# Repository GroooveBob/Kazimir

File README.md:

# Kazimir
Fightbox / Figtstick controler that runs wirh GP2040 firmware

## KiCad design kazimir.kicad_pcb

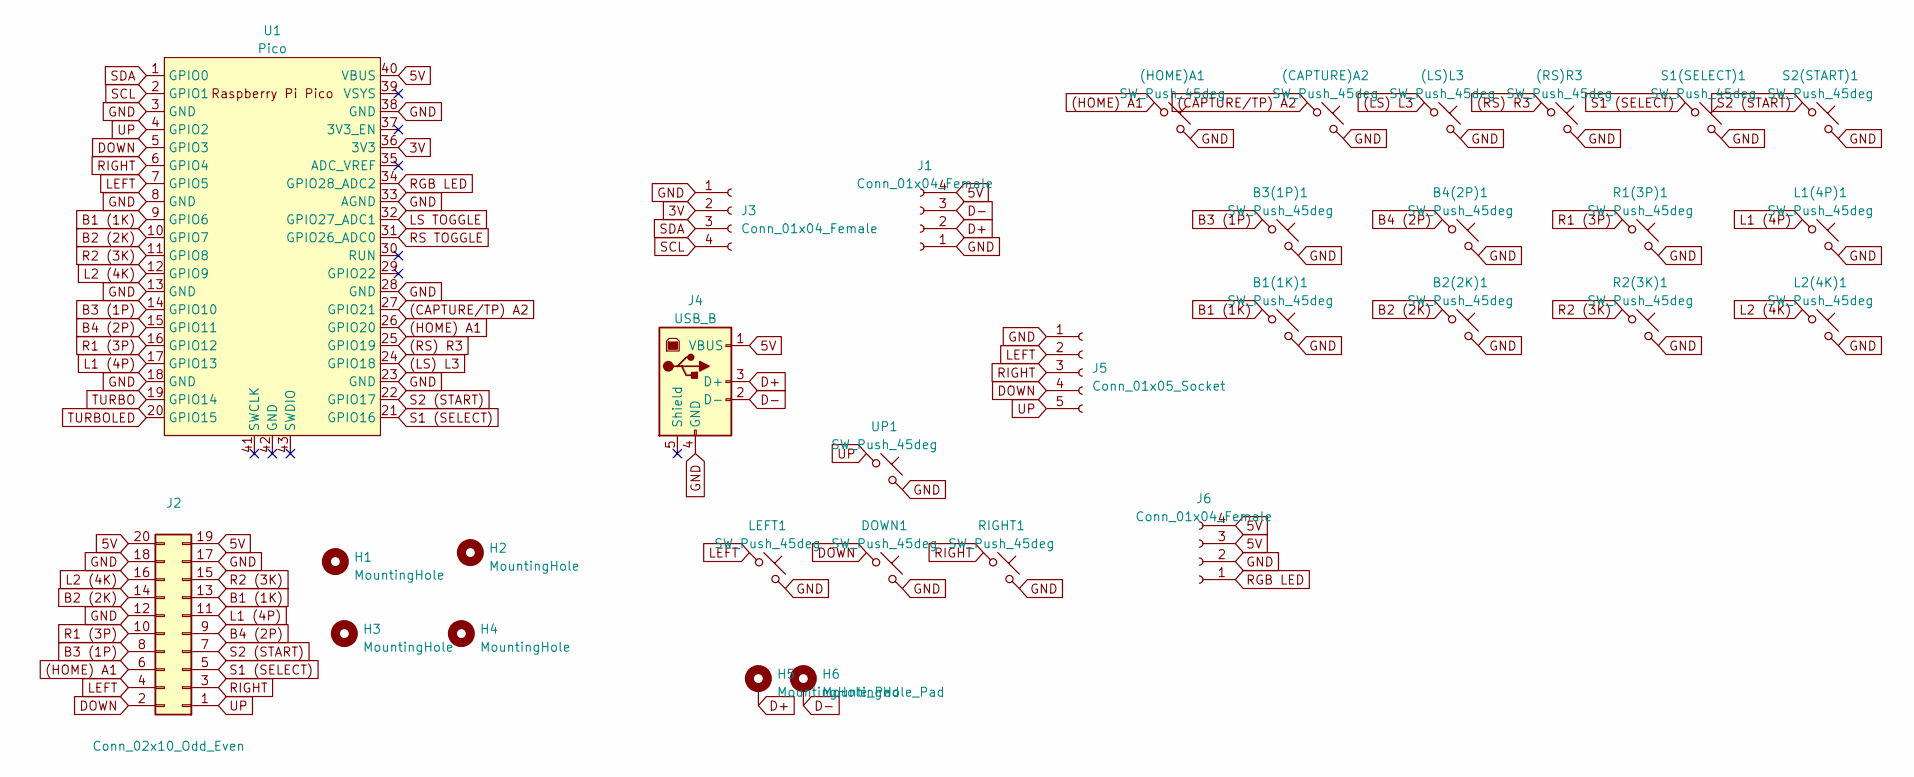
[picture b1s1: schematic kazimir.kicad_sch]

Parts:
(CAPTURE)A2: SW_Push_45deg; JST_XH_B2B-XH-A_1x02_P2.50mm_Verticalez
(HOME)A1: SW_Push_45deg; JST_XH_B2B-XH-A_1x02_P2.50mm_Verticalez
(LS)L3: SW_Push_45deg; JST_XH_B2B-XH-A_1x02_P2.50mm_Verticalez
(RS)R3: SW_Push_45deg; JST_XH_B2B-XH-A_1x02_P2.50mm_Verticalez
B1(1K)1, B2(2K)1, B3(1P)1, B4(2P)1: SW_Push_45deg; JST_XH_B2B-XH-A_1x02_P2.50mm_Verticalez
DOWN1: SW_Push_45deg; JST_XH_B2B-XH-A_1x02_P2.50mm_Verticalez
H1, H2, H3, H4: MountingHole; MountingHole_3.5mm_Pad_Via
H5, H6: MountingHole_Pad; TestPoint_Pad_2.5x2.5mm
J1, J3, J6: Conn_01x04_Female; JST_XH_B4B-XH-A_1x04_P2.50mm_Vertical
J2: Conn_02x10_Odd_Even; PinHeader_2x10_P2.54mm_Vertical
J4: USB_B; USB_B_Lumberg_2411_02_Horizontal
J5: Conn_01x05_Socket; JST_XH_B5B-XH-A_1x05_P2.50mm_Vertical
L1(4P)1, L2(4K)1: SW_Push_45deg; JST_XH_B2B-XH-A_1x02_P2.50mm_Verticalez
LEFT1: SW_Push_45deg; JST_XH_B2B-XH-A_1x02_P2.50mm_Verticalez
R1(3P)1, R2(3K)1: SW_Push_45deg; JST_XH_B2B-XH-A_1x02_P2.50mm_Verticalez
RIGHT1: SW_Push_45deg; JST_XH_B2B-XH-A_1x02_P2.50mm_Verticalez
S1(SELECT)1, S2(START)1: SW_Push_45deg; JST_XH_B2B-XH-A_1x02_P2.50mm_Verticalez
U1: Pico; RPi_Pico_SMD_TH
UP1: SW_Push_45deg; JST_XH_B2B-XH-A_1x02_P2.50mm_Verticalez

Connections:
3V: J3.2, U1.36 (3V3)
5V: J1.4, J2.19, J2.20, J4.1 (VBUS), J6.3, J6.4, U1.40 (VBUS)
(CAPTURE/TP) A2: (CAPTURE)A2.1, U1.27 (GPIO21)
(HOME) A1: (HOME)A1.1, J2.6, U1.26 (GPIO20)
(LS) L3: (LS)L3.1, U1.24 (GPIO18)
(RS) R3: (RS)R3.1, U1.25 (GPIO19)
B1 (1K): B1(1K)1.1, J2.13, U1.9 (GPIO6)
B2 (2K): B2(2K)1.1, J2.14, U1.10 (GPIO7)
B3 (1P): B3(1P)1.1, J2.8, U1.14 (GPIO10)
B4 (2P): B4(2P)1.1, J2.9, U1.15 (GPIO11)
D+: H5.1, J1.2, J4.3 (D+)
D-: H6.1, J1.3, J4.2 (D-)
DOWN: DOWN1.1, J2.2, J5.4, U1.5 (GPIO3)
GND: (CAPTURE)A2.2, (HOME)A1.2, (LS)L3.2, (RS)R3.2, B1(1K)1.2, B2(2K)1.2, B3(1P)1.2, B4(2P)1.2, DOWN1.2, J1.1, J2.12, J2.17, J2.18, J3.1, J4.4 (GND), J5.1, J6.2, L1(4P)1.2, L2(4K)1.2, LEFT1.2, R1(3P)1.2, R2(3K)1.2, RIGHT1.2, S1(SELECT)1.2, S2(START)1.2, U1.3 (GND), U1.8 (GND), U1.13 (GND), U1.18 (GND), U1.23 (GND), U1.28 (GND), U1.33 (AGND), U1.38 (GND), UP1.2
L1 (4P): J2.11, L1(4P)1.1, U1.17 (GPIO13)
L2 (4K): J2.16, L2(4K)1.1, U1.12 (GPIO9)
LEFT: J2.4, J5.2, LEFT1.1, U1.7 (GPIO5)
LS TOGGLE: U1.32 (GPIO27_ADC1)
R1 (3P): J2.10, R1(3P)1.1, U1.16 (GPIO12)
R2 (3K): J2.15, R2(3K)1.1, U1.11 (GPIO8)
RGB LED: J6.1, U1.34 (GPIO28_ADC2)
RIGHT: J2.3, J5.3, RIGHT1.1, U1.6 (GPIO4)
RS TOGGLE: U1.31 (GPIO26_ADC0)
S1 (SELECT): J2.5, S1(SELECT)1.1, U1.21 (GPIO16)
S2 (START): J2.7, S2(START)1.1, U1.22 (GPIO17)
SCL: J3.4, U1.2 (GPIO1)
SDA: J3.3, U1.1 (GPIO0)
TURBO: U1.19 (GPIO14)
TURBOLED: U1.20 (GPIO15)
UP: J2.1, J5.5, U1.4 (GPIO2), UP1.1

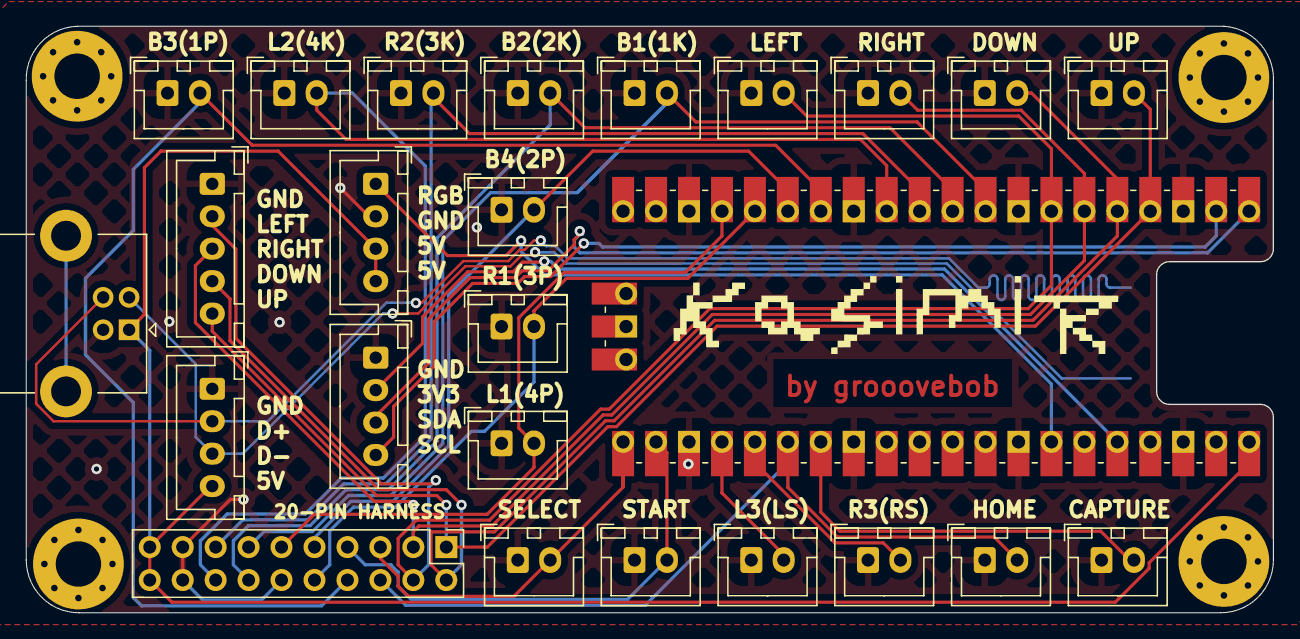
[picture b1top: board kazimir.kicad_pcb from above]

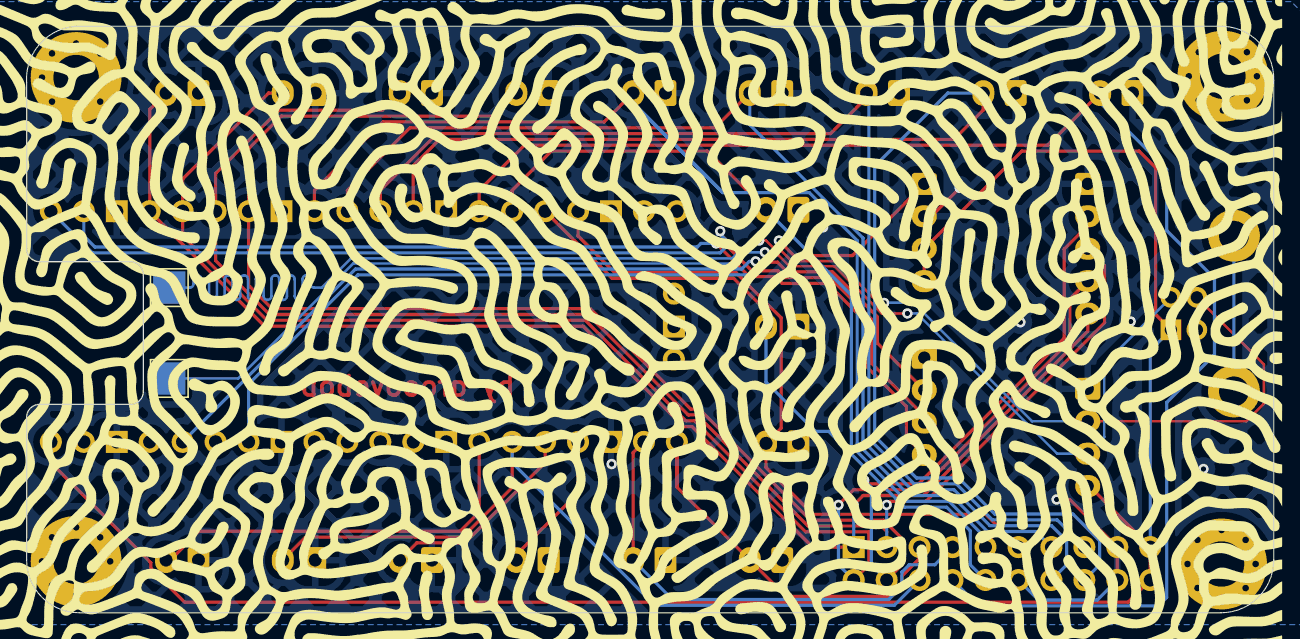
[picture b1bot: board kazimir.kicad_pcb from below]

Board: 2 copper layers, 96.1 x 45.2 mm, 31 parts (2 on the bottom side), 26 nets.

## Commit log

2023-05-20 pics
